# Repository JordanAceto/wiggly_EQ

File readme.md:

## Rackmount 3-Band Parametric EQ and Compression FX unit

### [SCHEMATIC](https://github.com/JordanAceto/wiggly_EQ/blob/main/construction_docs/wiggly_EQ_schematic.pdf)

### Features:
#### 3 bands of Parametric EQ
- boost/cut control
- Q control
- Center frequency control
- Voltage controlled frequency for wiggly and swooshy modulation effects

#### Compression
- Nice THAT compressor
- Ratio control
- Threshold control
- Makeup gain

#### LFO
- Wiggles the EQ stages
- Also does amplitude modulation for tremolo

#### Expression pedal input
- Works as a Volume pedal
- Can also control the LFO rate

#### LED bar graph meter
- Can indicate compression gain reduction
- Can also indicate the audio level at -10dBv or +4dBu

### Notes:
- this is an old project that I built on pad-per-hole prototyping board. There is no PCB layout.
- I would probably do a few things differently today, but it does work well and sounds good.
- there are a few missing values, and some that I had to guess about, it's probably pretty close to right, but there might be some errors.
- there is a map of the protoboard IC locations as a troubleshooting and modification aid

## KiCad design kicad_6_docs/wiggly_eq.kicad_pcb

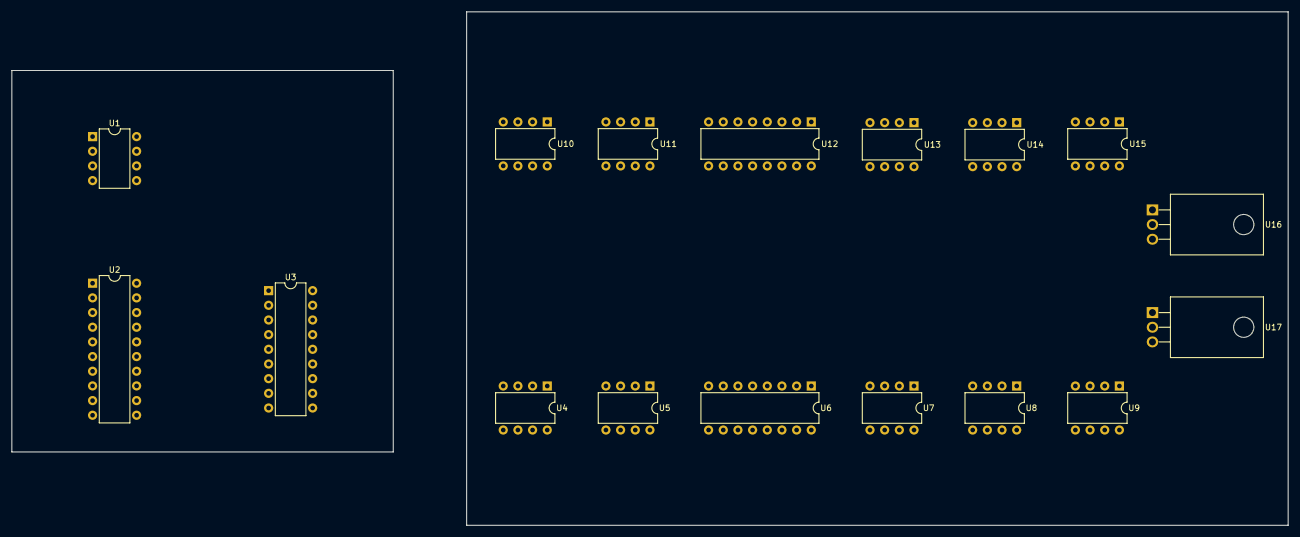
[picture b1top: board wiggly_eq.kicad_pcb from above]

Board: 2 copper layers, 142.2 x 88.9 mm, 17 parts (0 on the bottom side), 22 nets, no tracks yet.

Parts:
U1: NE5532; DIP-8_W7.62mm
U2: THAT4301; DIP-20_W7.62mm
U3: LM3914N; DIP-18_W7.62mm
U4, U5, U7, U8, U9, U10, U11, U13, U14, U15: TL072; DIP-8_W7.62mm
U6, U12: SSI2164; DIP-16_W7.62mm
U16: LM317_TO-220; TO-220F-3_Horizontal_TabDown
U17: LM337_TO220; TO-220F-3_Horizontal_TabDown

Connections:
+15V: U1.8 (V+), U2.11 (Vcc), U3.3 (V+), U3.9 (MODE), U4.8 (V+), U5.8 (V+), U6.16 (V+), U7.8 (V+), U8.8 (V+), U9.8 (V+), U10.8 (V+), U11.8 (V+), U12.16 (V+), U13.8 (V+), U14.8 (V+), U15.8 (V+), U16.2 (VO)
-15V: U1.4 (V-), U2.10 (Vee), U4.4 (V-), U5.4 (V-), U6.9 (V-), U7.4 (V-), U8.4 (V-), U9.4 (V-), U10.4 (V-), U11.4 (V-), U12.9 (V-), U13.4 (V-), U14.4 (V-), U15.4 (V-), U17.3 (VO)
/parametric_EQ/high_band_eq/Vfc: U12.11, U12.14, U15.7
/parametric_EQ/low_band_eq/Vfc: U6.11, U6.14, U9.7
/parametric_EQ/mid_band_eq/Vfc: U6.3, U6.6, U9.1
GND: U1.5 (+), U2.8 (+), U2.9 (GND), U2.15 (EC+), U2.20 (+), U3.2 (V-), U3.4 (RLO), U3.8 (REFADJ), U6.8 (gnd), U7.3 (+), U7.5 (+), U8.3 (+), U8.5 (+), U9.3 (+), U9.5 (+), U10.3 (+), U11.3 (+), U12.8 (gnd), U13.2 (-), U13.5 (+), U14.3 (+), U14.5 (+), U15.2 (-), U15.5 (+)
unnamed: U6.5, U7.2 (-)
unnamed: U4.3 (+), U7.1
unnamed: U6.4, U8.2 (-)
unnamed: U12.12, U13.6 (-)
unnamed: U10.5 (+), U13.7
unnamed: U12.13, U14.6 (-)
unnamed: U12.4, U14.2 (-)
unnamed: U12.3, U13.1
unnamed: U2.7, U2.16 (EC-)
unnamed: U11.2 (-), U12.5
unnamed: U10.1, U12.6
unnamed: U6.12, U7.6 (-)
unnamed: U4.5 (+), U7.7
unnamed: U6.13, U8.6 (-)
unnamed: U3.6 (RHI), U3.7 (REFOUT)
unnamed: U1.1, U1.2 (-)

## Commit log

2022-05-29 Fix schematic link
2022-08-01 Fix power supply errors, tidy up schematic
2023-02-04 Add some images, update readme

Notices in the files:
kicad_6_docs/wiggly_eq.kicad_pcb:
creativecommons.org/licenses/by/4.0
License: CC by 4.0
